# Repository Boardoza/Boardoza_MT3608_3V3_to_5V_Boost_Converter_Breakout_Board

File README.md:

# Boardoza MT3608 Boost Converter Breakout Board

The **Boardoza MT3608 Breakout Board** is a compact and efficient DC-DC boost converter solution designed around the **MT3608** high-frequency switching regulator IC. This board converts low DC input voltages into a stable and regulated higher output voltage, making it suitable for battery-powered and embedded electronics applications where voltage boosting is required.

Configured for a typical **3.3V to 5V conversion**, this breakout board is ideal for powering 5V logic circuits, sensors, wireless modules, and microcontroller-based systems from low-voltage power sources such as Li-ion batteries or low-voltage adapters. Thanks to its compact form factor and high conversion efficiency, it can be integrated into portable electronics, IoT devices, robotics, and industrial control projects.

## [Click here to purchase!](https://www.ozdisan.com/ureticiler/boardoza)

| Front Side | Back Side |
|:---:|:---:|
|  |  |

---

## Key Features

- **MT3608 Boost Converter IC:** Designed using the MT3608 high-efficiency DC-DC step-up converter.
- **3.3V to 5V Conversion:** Optimized to boost a 3.3V input into a stable 5V regulated output.
- **High Efficiency Design:** Provides up to 97% efficiency for low power loss and improved battery life.  
- **Automatic PFM (Pulse Frequency Modulation) Mode:** Improves efficiency during light-load operation.
- **Wide Application Range:** Suitable for IoT devices, battery-powered systems, robotics, and portable electronics.

---

## Technical Specifications

**Model:** MT3608   
**Manufacturer:** Boardoza  
**Manufacturer IC:** Aerosemi Technology  
**Input Voltage:** 3.3V  
**Output Voltage:** 5V  
**Output Current:** Up to 500mA  
**Functions:** DC-DC Step-Up (Boost) Converter  
**Switching Frequency:** 1.2MHz  
**Efficiency:** Up to 97%  
**Control Method:** Current Mode PWM  
**Operating Temperature:** -40°C to +85°C  
**Board Dimensions:** 40mm x 20mm  

---

## Board Pinout

### ( J1 ) Input Connector

| Pin Number | Pin Name | Description |
|:---:|:---:|---|
| 1 | VIN | Input Supply Voltage (3.3V) |
| 2 | GND | Ground |

### ( J2 ) Output Connector

| Pin Number | Pin Name | Description |
|:---:|:---:|---|
| 1 | VOUT | Regulated Output Voltage (5V) |
| 2 | GND | Ground |

---

## Board Dimensions

---

## Step Files

[Boardoza MT3608.step](./assets/MT3608%20Step.step)

---

## Datasheet

[MT3608 Datasheet.pdf](./assets/MT3608%20Datasheet.pdf)  

---

## Version History

- V1.0.0 - Initial Release

---

## Support

- If you have any questions or need support, please contact support@boardoza.com

---

## **License**
### **Hardware Design**

[![CC BY-SA 4.0][cc-by-sa-shield]][cc-by-sa]

All hardware design files are licensed under [Creative Commons Attribution-ShareAlike 4.0 International License][cc-by-sa].

[cc-by-sa]: http://creativecommons.org/licenses/by-sa/4.0/
[cc-by-sa-shield]: https://img.shields.io/badge/License-CC%20BY--SA%204.0-lightgrey.svg

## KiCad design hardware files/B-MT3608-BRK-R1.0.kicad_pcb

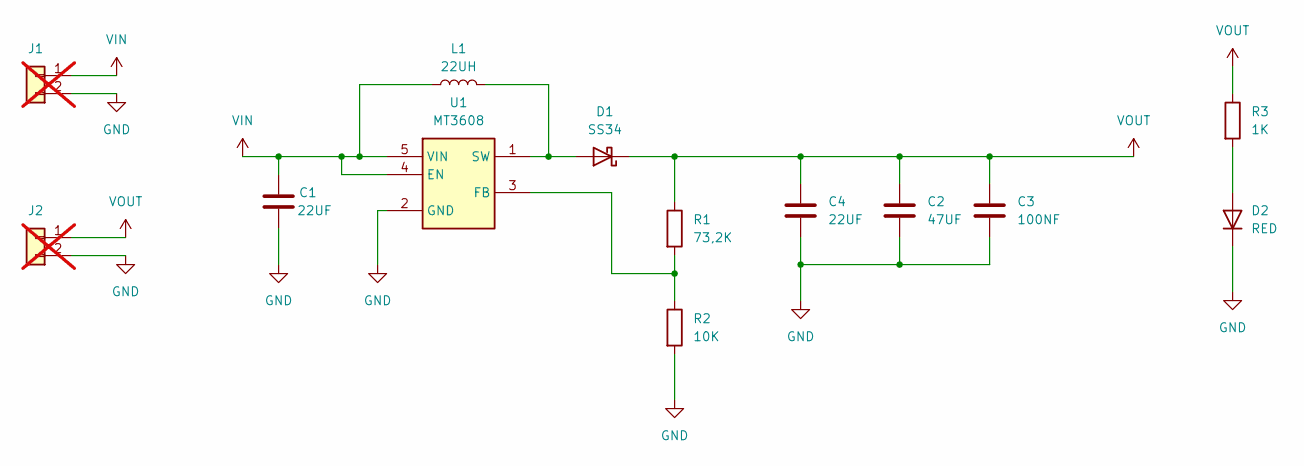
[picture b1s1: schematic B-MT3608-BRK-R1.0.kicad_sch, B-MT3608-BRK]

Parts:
C1: 22UF; C_0603_1608Metric; MPN GRM188R61A226ME15D
C2: 47UF; C_0805_2012Metric; MPN CL21A476MQYNNNE
C3: 100NF; C_0805_2012Metric; MPN CL21B104KACNNNC
C4: 22UF; C_0805_2012Metric; MPN CL21A226MQQNNNE
D1: SS34; D_SMC; MPN SS34C-MD
D2: RED; D_0603_1608Metric; MPN LTST-C190KRKT
J1, J2: Conn_01x02; 2317-02S_1x02_P2.50mm_Vertical; MPN 2317-02S; not fitted
L1: 22UH; L_10X9; MPN FPI1005-220M
R1: 73,2K; R_0603_1608Metric; MPN 0603SAF7322T5E
R2: 10K; R_0603_1608Metric; MPN 0603SAJ0103T5E
R3: 1K; R_0603_1608Metric; MPN CRT03J7E1001
U1: MT3608; SOT-23-6; MPN MT3608-

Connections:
GND: C1.1, C2.2, C3.2, C4.2, D2.1 (K), J1.2, J2.2, R2.2, U1.2 (GND)
unnamed: D1.2 (A), L1.2, U1.1 (SW)
unnamed: D2.2 (A), R3.2
unnamed: R1.2, R2.1, U1.3 (FB)
VIN: C1.2, J1.1, L1.1, U1.4 (EN), U1.5 (VIN)
VOUT: C2.1, C3.1, C4.1, D1.1 (K), J2.1, R1.1, R3.1

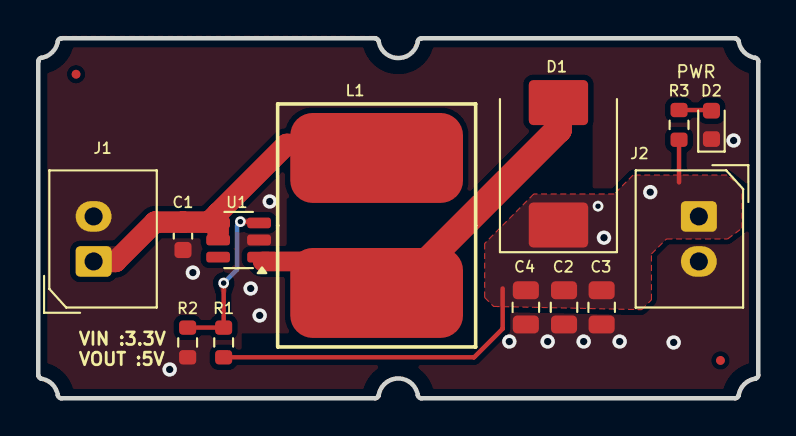
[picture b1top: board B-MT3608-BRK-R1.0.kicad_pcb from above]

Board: 2 copper layers, 40.0 x 20.0 mm, 13 parts (0 on the bottom side), 6 nets.
